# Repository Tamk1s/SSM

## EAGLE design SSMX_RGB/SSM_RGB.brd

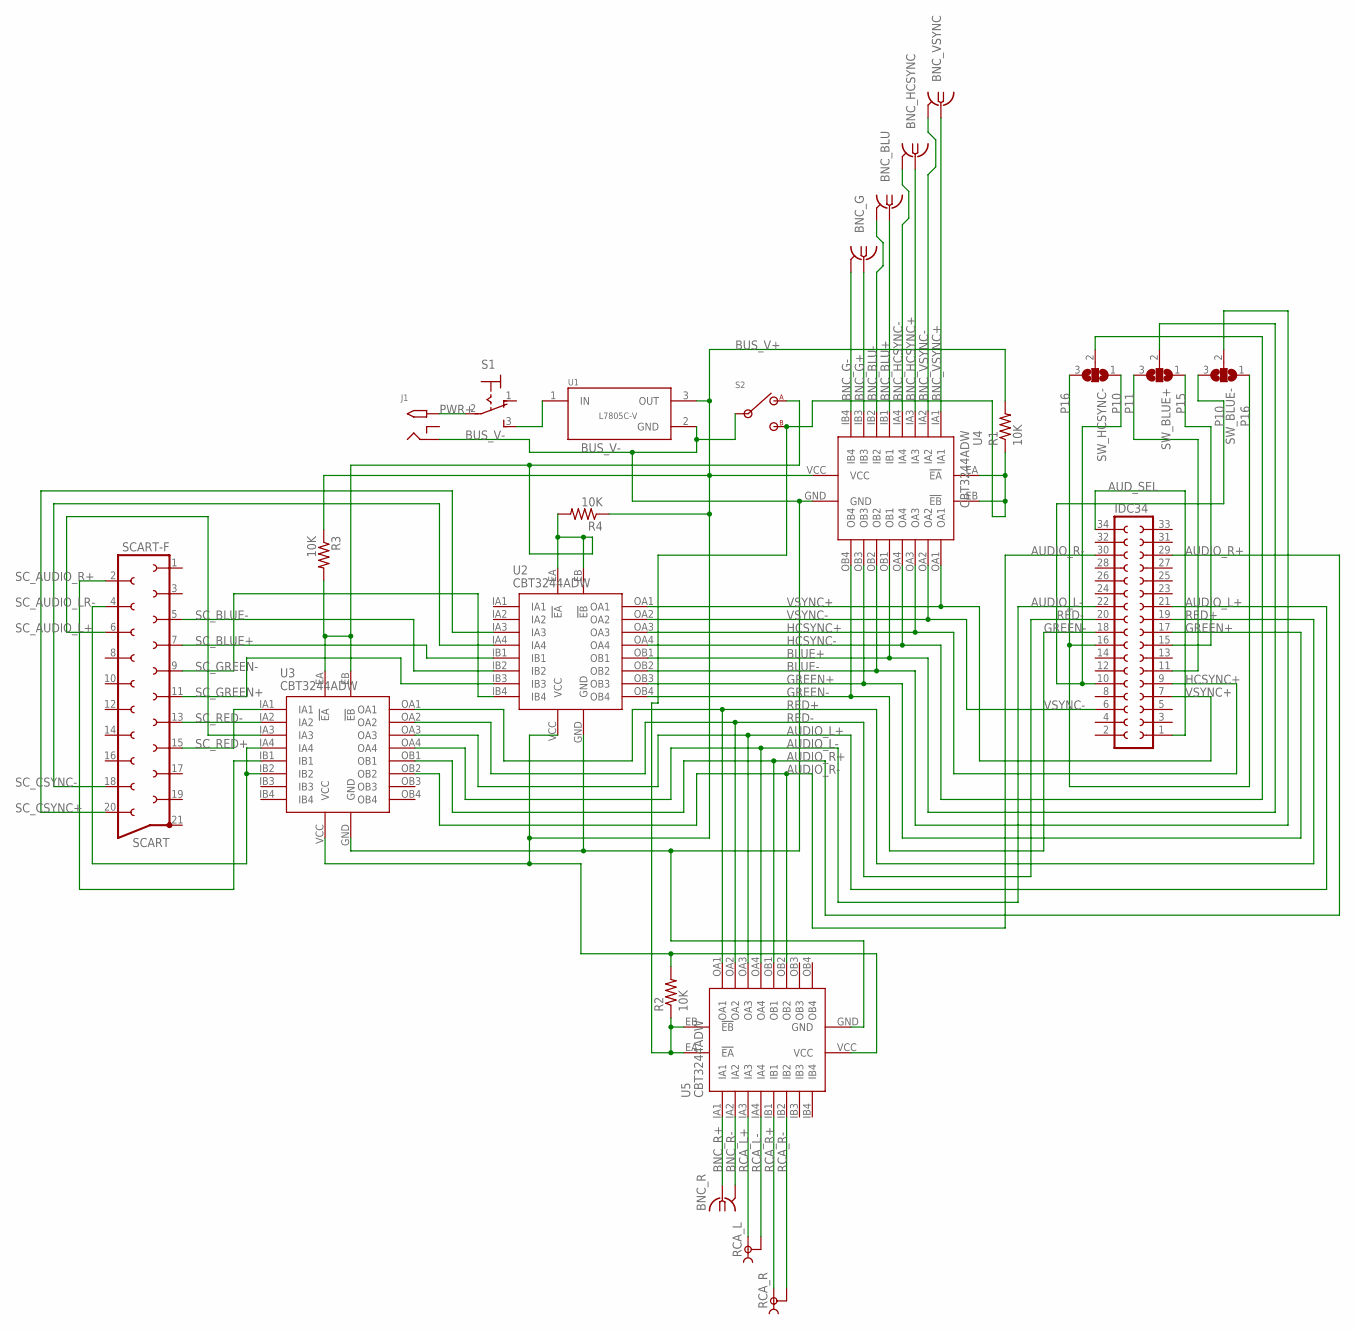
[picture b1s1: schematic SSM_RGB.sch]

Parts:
BNC_BLU: 142142
BNC_G: 142142
BNC_HCSYNC: 142142
BNC_R: 142142
BNC_VSYNC: 142142
IDC34: SOCKET-34RA; S34RA
J1: 2.1MMJACKTHM; PJ-102A
R1, R2, R3, R4: 10K; 0207/10
RCA_L: TOBU3
RCA_R: TOBU3
S1: 320-916
S2: STS121PC04
SCART: SCART-F
SW_BLUE+: SJ2W; SJ_2
SW_BLUE-: SJ2W; SJ_2
SW_HCSYNC-: SJ2W; SJ_2
U1: L7805C-V; TO254P460X1020X1945-3P
U2, U3, U4, U5: CBT3244ADW; SOIC-20

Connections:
AUDIO_L+: IDC34.21, U3.OA3, U5.OA3
AUDIO_L-: IDC34.22, U3.OA4, U5.OA4
AUDIO_R+: IDC34.29, U3.OB1, U5.OB1
AUDIO_R-: IDC34.30, U3.OB2, U5.OB2
AUD_SEL: IDC34.1, IDC34.34
BLUE+: SW_BLUE+.2, U2.OB1, U4.OB1
BLUE-: SW_BLUE-.2, U2.OB2, U4.OB2
BNC_BLU+: BNC_BLU.1, U4.IB1
BNC_BLU-: BNC_BLU.2, BNC_BLU.3 (2), BNC_BLU.4 (2), BNC_BLU.5 (2), U4.IB2
BNC_G+: BNC_G.1, U4.IB3
BNC_G-: BNC_G.2, BNC_G.3 (2), BNC_G.4 (2), BNC_G.5 (2), U4.IB4
BNC_HCSYNC+: BNC_HCSYNC.1, U4.IA3
BNC_HCSYNC-: BNC_HCSYNC.2, BNC_HCSYNC.3 (2), BNC_HCSYNC.4 (2), BNC_HCSYNC.5 (2), U4.IA4
BNC_R+: BNC_R.1, U5.IA1
BNC_R-: BNC_R.2, BNC_R.3 (2), BNC_R.4 (2), BNC_R.5 (2), U5.IA2
BNC_VSYNC+: BNC_VSYNC.1, U4.IA1
BNC_VSYNC-: BNC_VSYNC.2, BNC_VSYNC.3 (2), BNC_VSYNC.4 (2), BNC_VSYNC.5 (2), U4.IA2
BUS_V+: R1.2, R2.2, R3.1, R4.1, U1.3 (OUT), U2.VCC, U3.VCC, U4.VCC, U5.VCC
BUS_V-: J1.RING, S2.2, U1.2 (GND), U2.GND, U3.GND, U4.GND, U5.GND
GREEN+: IDC34.17, U2.OB3, U4.OB3
GREEN-: IDC34.18, U2.OB4, U4.OB4
HCSYNC+: IDC34.9, U2.OA3, U4.OA3
HCSYNC-: SW_HCSYNC-.2, U2.OA4, U4.OA4
unnamed: R1.1, R2.1, S2.3, U4.EA (!EA), U4.EB (!EB), U5.EA (!EA), U5.EB (!EB)
unnamed: S1.3 (S), U1.1 (IN)
unnamed: R3.2, R4.2, S2.1, U2.EA (!EA), U2.EB (!EB), U3.EA (!EA), U3.EB (!EB)
P10: IDC34.10, SW_BLUE-.3, SW_HCSYNC-.1
P11: IDC34.11, SW_BLUE+.3
P15: IDC34.15, SW_BLUE+.1
P16: IDC34.16, SW_BLUE-.1, SW_HCSYNC-.3
PWR+: J1.TIP, S1.2
RCA_L+: RCA_L.1, U5.IA3
RCA_L-: RCA_L.2, RCA_L.2@1 (2), RCA_L.2@2 (2), U5.IA4
RCA_R+: RCA_R.1, U5.IB1
RCA_R-: RCA_R.2, RCA_R.2@1 (2), RCA_R.2@2 (2), U5.IB2
RED+: IDC34.19, U3.OA1, U5.OA1
RED-: IDC34.20, U3.OA2, U5.OA2
SC_AUDIO_L+: SCART.6, U3.IA3
SC_AUDIO_LR-: SCART.4, U3.IA4, U3.IB2
SC_AUDIO_R+: SCART.2, U3.IB1
SC_BLUE+: SCART.7, U2.IB1
SC_BLUE-: SCART.5, U2.IB2
SC_CSYNC+: SCART.20, U2.IA3
SC_CSYNC-: SCART.18, U2.IA4
SC_GREEN+: SCART.11, U2.IB3
SC_GREEN-: SCART.9, U2.IB4
SC_RED+: SCART.15, U3.IA1
SC_RED-: SCART.13, U3.IA2
VSYNC+: IDC34.7, U2.OA1, U4.OA1
VSYNC-: IDC34.6, U2.OA2, U4.OA2

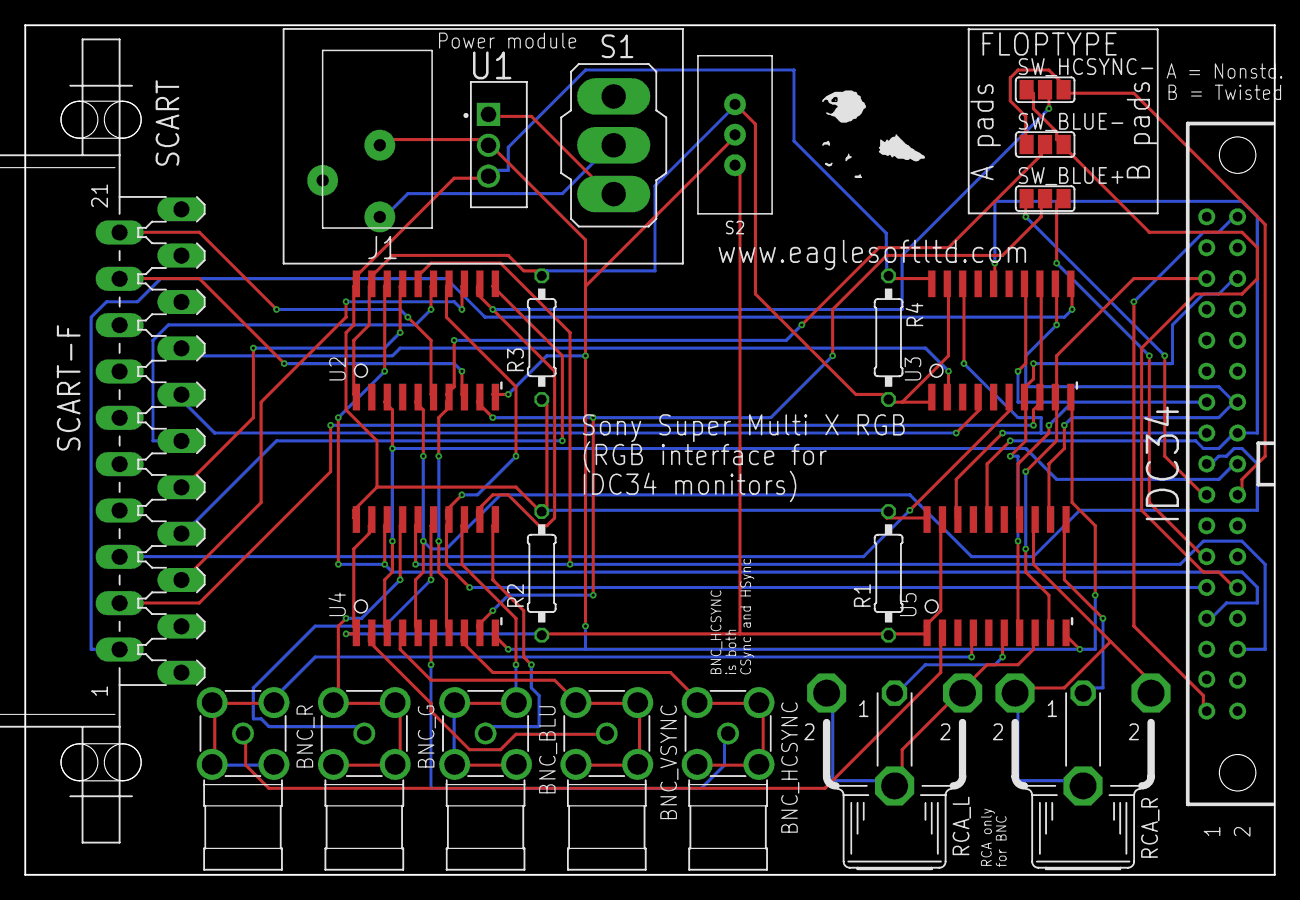
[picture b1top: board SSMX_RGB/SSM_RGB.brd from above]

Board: 2 copper layers, 102.7 x 69.8 mm, 24 parts (0 on the bottom side), 50 nets.

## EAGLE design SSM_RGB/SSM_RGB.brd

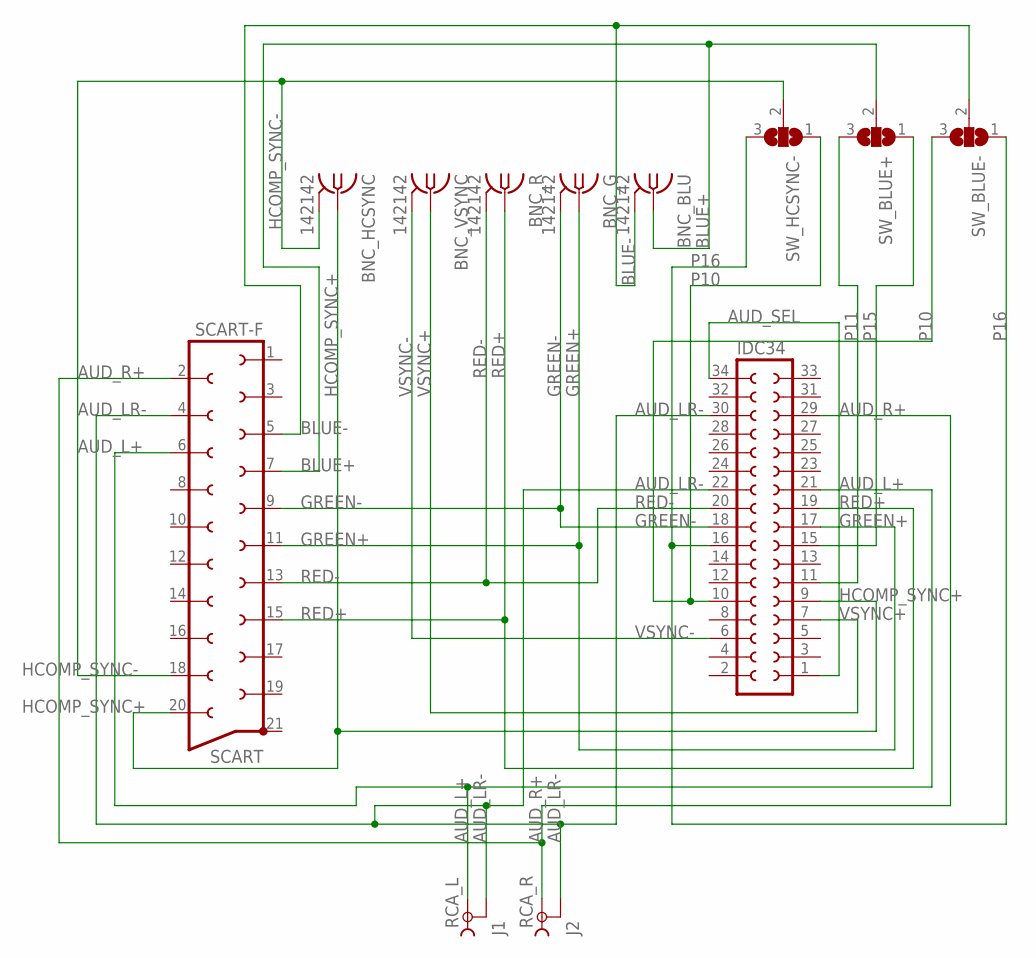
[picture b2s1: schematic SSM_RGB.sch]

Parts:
BNC_BLU: 142142
BNC_G: 142142
BNC_HCSYNC: 142142
BNC_R: 142142
BNC_VSYNC: 142142
IDC34: SOCKET-34RA; S34RA
RCA_L: J1; TOBU3
RCA_R: J2; TOBU3
SCART: SCART-F
SW_BLUE+: SJ2W; SJ_2
SW_BLUE-: SJ2W; SJ_2
SW_HCSYNC-: SJ2W; SJ_2

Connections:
AUD_L+: IDC34.21, RCA_L.1, SCART.6
AUD_LR-: IDC34.22, IDC34.30, RCA_L.2, RCA_L.2@1 (2), RCA_L.2@2 (2), RCA_R.2, RCA_R.2@1 (2), RCA_R.2@2 (2), SCART.4
AUD_R+: IDC34.29, RCA_R.1, SCART.2
AUD_SEL: IDC34.1, IDC34.34
BLUE+: BNC_BLU.1, SCART.7, SW_BLUE+.2
BLUE-: BNC_BLU.2, BNC_BLU.3 (2), BNC_BLU.4 (2), BNC_BLU.5 (2), SCART.5, SW_BLUE-.2
GREEN+: BNC_G.1, IDC34.17, SCART.11
GREEN-: BNC_G.2, BNC_G.3 (2), BNC_G.4 (2), BNC_G.5 (2), IDC34.18, SCART.9
HCOMP_SYNC+: BNC_HCSYNC.1, IDC34.9, SCART.20
HCOMP_SYNC-: BNC_HCSYNC.2, BNC_HCSYNC.3 (2), BNC_HCSYNC.4 (2), BNC_HCSYNC.5 (2), SCART.18, SW_HCSYNC-.2
P10: IDC34.10, SW_BLUE-.3, SW_HCSYNC-.1
P11: IDC34.11, SW_BLUE+.3
P15: IDC34.15, SW_BLUE+.1
P16: IDC34.16, SW_BLUE-.1, SW_HCSYNC-.3
RED+: BNC_R.1, IDC34.19, SCART.15
RED-: BNC_R.2, BNC_R.3 (2), BNC_R.4 (2), BNC_R.5 (2), IDC34.20, SCART.13
VSYNC+: BNC_VSYNC.1, IDC34.7
VSYNC-: BNC_VSYNC.2, BNC_VSYNC.3 (2), BNC_VSYNC.4 (2), BNC_VSYNC.5 (2), IDC34.6

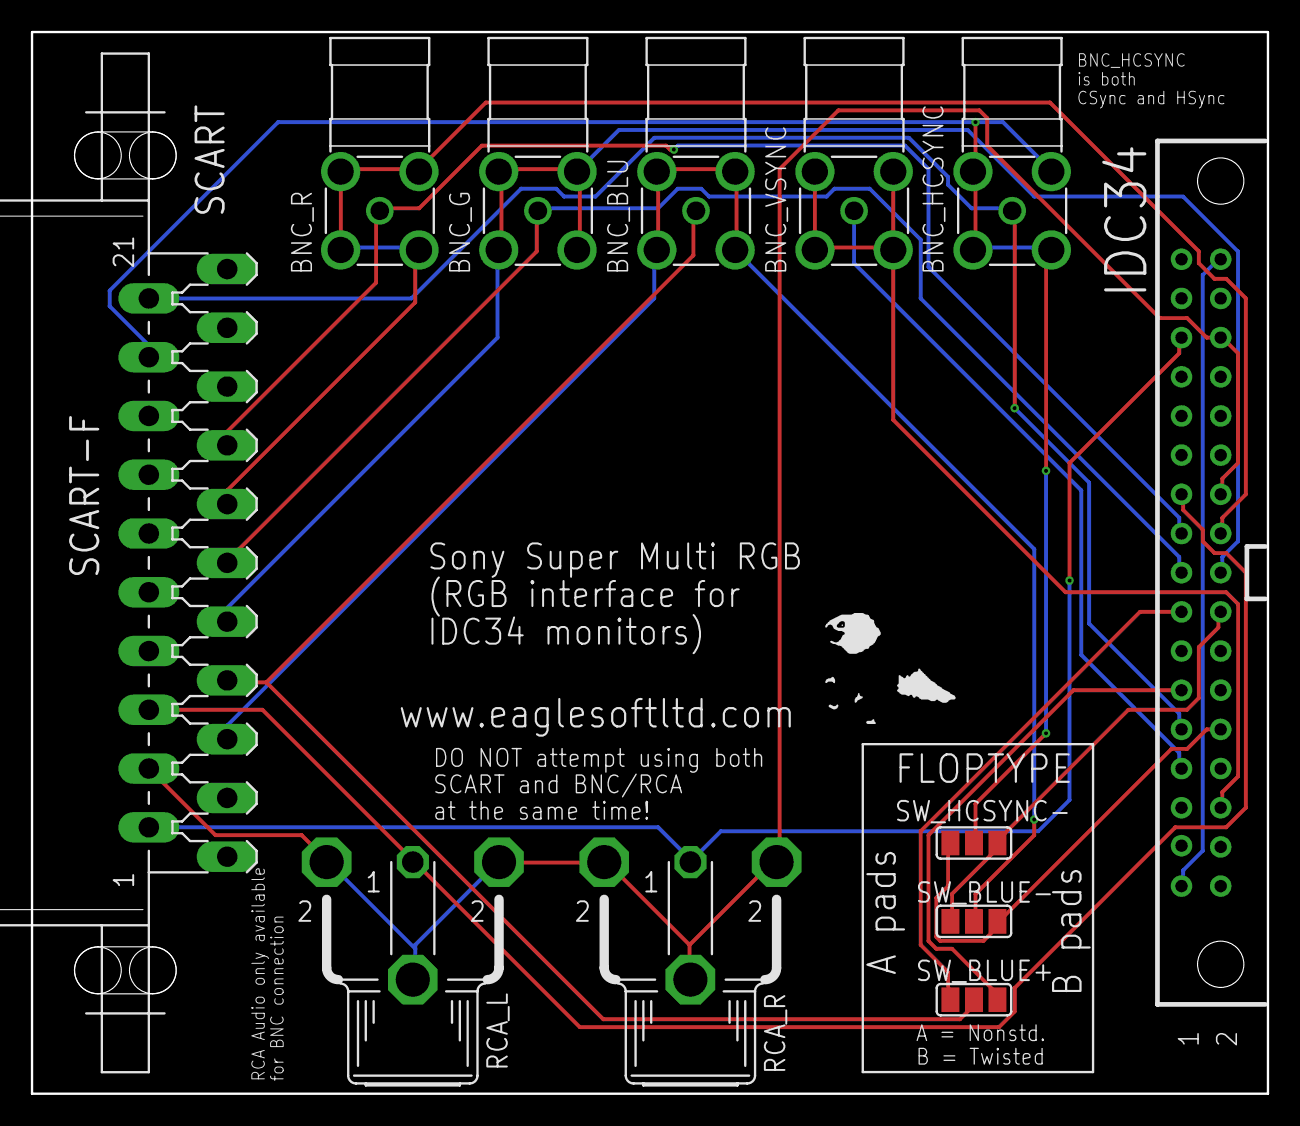
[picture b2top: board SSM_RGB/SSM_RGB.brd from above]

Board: 2 copper layers, 80.1 x 68.8 mm, 12 parts (0 on the bottom side), 18 nets.

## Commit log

2018-07-29 Clarification for normal vs. twisted floppy mapping
2018-08-03 Updated logo
    *Fixed bug with logo not appearing with proper colors. (Made beak and brown wings copper gold)
2018-08-06 Updated previews
2018-08-13 Revision
    *Tied S_PWR Pos 1 to nothing (no power on this pos)
    *Addressed errors and warnings in ERC
    *Ran Autorouter again to fix netlist
2018-08-30 Final PCB revisions
    SSM & X:
    *Renamed BNC_HComp_Sync to just BNC_HCSYNC
    *Renamed "Normal" cable type to "Nonstd"
    *Removed stray line segs in PCB Art
    SSM:
    *Added warning about using both AV sources
2018-08-31 Updated pics, manual, BOM
    *Updated manuals with footprint names/labels for directions
    *Updated project artwork
    *Updated a trace on SSMX board, so that it doesn't go through copper-clad Eagle PCB
    *Updated BOM with more accurate, nearly final pricing. Added bagging costs. floppy cable costs
2018-09-01 BOM update
    *Swapped out expensive x5 BNC pair from Digikey (~$18) with pricing based on a lot of 100 from eBay ($5 per kit)
    *Fixed typo in SSMX manual for header
2018-09-04 Updated BOM/manual
2018-09-10 BOM Update
    Updated BOM costs with:
    *Package shipping
    *Crayon Box enclosure
    *Updated bagging costs
2018-09-10 Safety
2018-12-10 Fixes todo
2019-12-25 Misc commit
    *Uploaded archive of pics
    *Updated Revisions Notes
    I need to implement changes in the revisions Notes doc, fabricated corrected prototype boards (correct footprints), fully test them, and finally release/sell these kits early this year !!
2022-02-05 Details about composite video revision
    - Added new links for S-Video<->SCART conversion (using those composite/S-Video<->SCART I/O adapters)
    - Added S-Video pinout link
    Details for these to be implemented in next revision of SSM(X) circuits, to tie 4 pins for S-Video/composite video support. This will allow Composite/S-Video<->SCART I/O adapters to work with the cir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
    (Target/example usage case: CLD-D702 Laserdisc player S-Video support on this RGB monitor. S-Video utilizes 480p video on the LD player, allowing for higher resolution/RGB video on the player)
